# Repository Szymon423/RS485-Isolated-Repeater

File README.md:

# RS485 Isolated Repeater

This project is abotut designing an isolated repeater for RS485 communication. As a person who many times had to deal with RS485 communication, I know how important it is to have a repeater in order to extend the communication distance. However, I also know how important it is to have an isolated repeater in order to avoid ground loops and other issues that can arise from non-isolated repeaters. This project is about designing an isolated repeater that can be used to extend the communication distance of RS485 devices. The repeater is designed to be used with a `12..24V` power supply and can be used to extend the communication distance up to 1000 meters. 

> [!IMPORTANT]
> Chad GPT is amazing and made up this trash talk above.

To be honest this is not about extending range of RS485 loop, even though it can be used for that. It is about isolating the RS485 devices which are shitty and can cause problems. 

> [!NOTE]
> I want to help people who made shitty RS485 bus or RS485 devices.

## Tools stack
- Hardware design: `KiCad`
- PCB manufacturing: `JLCPCB`
- Microcontroller code: `Raspberry Pi Pico Extension for VSCode`
- Knowledge: `IDK`

## Hardware
{:width="200px"}

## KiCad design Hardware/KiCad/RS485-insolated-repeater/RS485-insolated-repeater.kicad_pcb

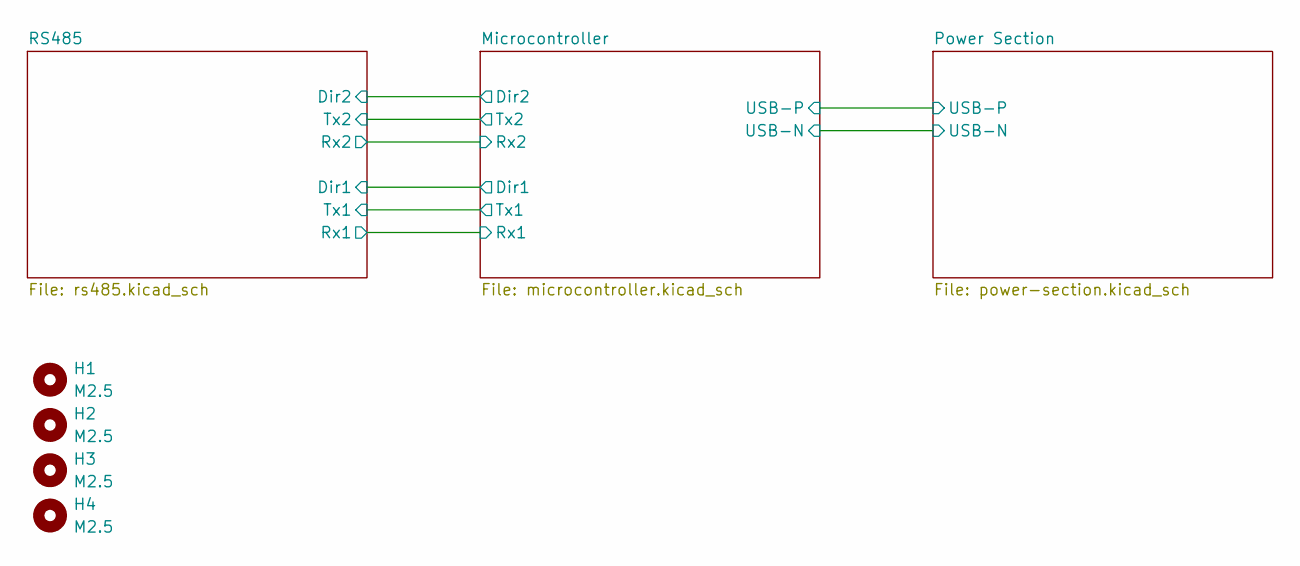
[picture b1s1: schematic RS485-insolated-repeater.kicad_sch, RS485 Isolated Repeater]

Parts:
H1, H2, H3, H4: M2.5; MountingHole_2.7mm_M2.5

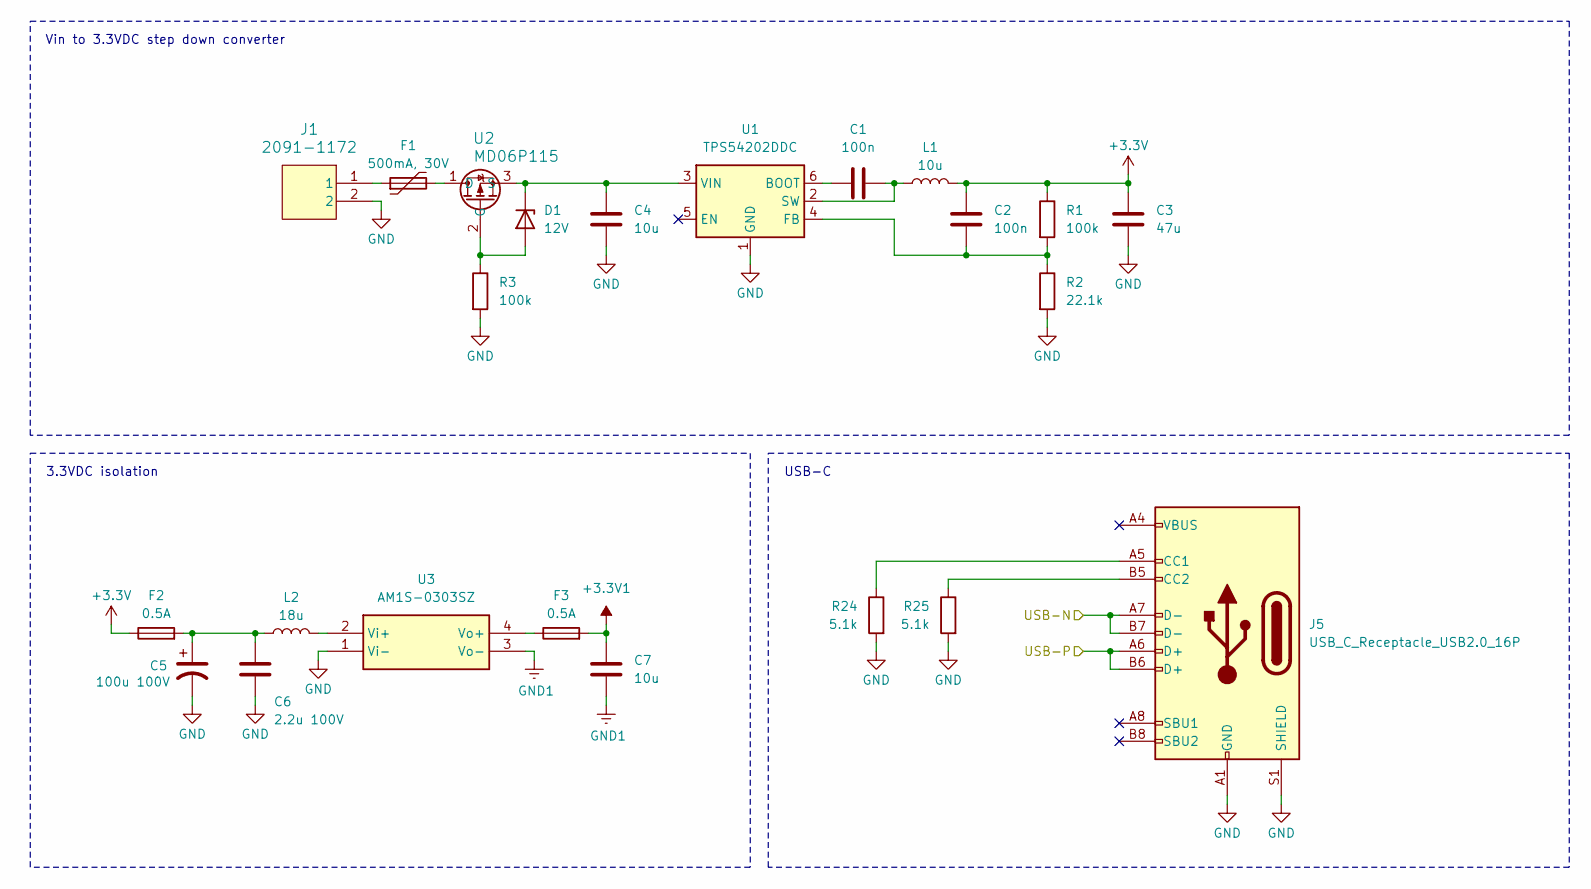
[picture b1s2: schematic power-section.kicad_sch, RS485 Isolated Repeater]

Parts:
C1, C2: 100n; C_0805_2012Metric
C3: 47u; C_1206_3216Metric
C4, C7: 10u; C_1206_3216Metric
C5: 100u 100V; CP_Radial_D10.0mm_P5.00mm
C6: 2.2u 100V; C_1210_3225Metric
D1: 12V; D_SMA
F1: 500mA, 30V; Fuse_1812_4532Metric
F2, F3: 0.5A; Fuse_1206_3216Metric
J1: 2091-1172
J5: USB_C_Receptacle_USB2.0_16P; USB_C_Receptacle_GCT_USB4105-xx-A_16P_TopMnt_Horizontal
L1: 10u; L_12x12mm_H4.5mm
L2: 18u; L_Ferrocore_DLG-0504
R1, R3: 100k; R_0805_2012Metric
R2: 22.1k; R_0805_2012Metric
R24, R25: 5.1k; R_0805_2012Metric
U1: TPS54202DDC; SOT-23-6
U2: MD06P115
U3: AM1S-0303SZ; SON50P300X200X60-9N; Manufacturer_Part_Number W25Q16JVUXIQ TR

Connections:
+3.3V: C2.2, C3.2, F2.1, L1.2, R1.1; also elsewhere on the board
+3.3V1: C7.2, F3.2; also elsewhere on the board
/Microcontroller/USB-N: J5.A7 (D-), J5.B7 (D-); also elsewhere on the board
/Microcontroller/USB-P: J5.A6 (D+), J5.B6 (D+); also elsewhere on the board
GND: C3.1, C4.1, C5.2, C6.2, J1.2, J5.A1 (GND), J5.A12 (GND), J5.B1 (GND), J5.B12 (GND), J5.S1 (SHIELD), R2.2, R3.2, R24.2, R25.2, U1.1 (GND), U3.1 (Vi-); also elsewhere on the board
GND1: C7.1, U3.3 (Vo-); also elsewhere on the board
unnamed: C5.1, C6.1, F2.2, L2.1
unnamed: D1.2 (A), R3.1, U2.2 (G)
unnamed: C4.2, D1.1 (K), U1.3 (VIN), U2.3 (S)
unnamed: F1.1, J1.1
unnamed: J5.A5 (CC1), R24.1
unnamed: J5.B5 (CC2), R25.1
unnamed: C1.1, U1.6 (BOOT)
unnamed: C2.1, R1.2, R2.1, U1.4 (FB)
unnamed: C1.2, L1.1, U1.2 (SW)
unnamed: F1.2, U2.1 (D)
unnamed: L2.2, U3.2 (Vi+)
unnamed: F3.1, U3.4 (Vo+)

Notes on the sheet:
Vin to 3.3VDC step down converter
USB-C
3.3VDC isolation

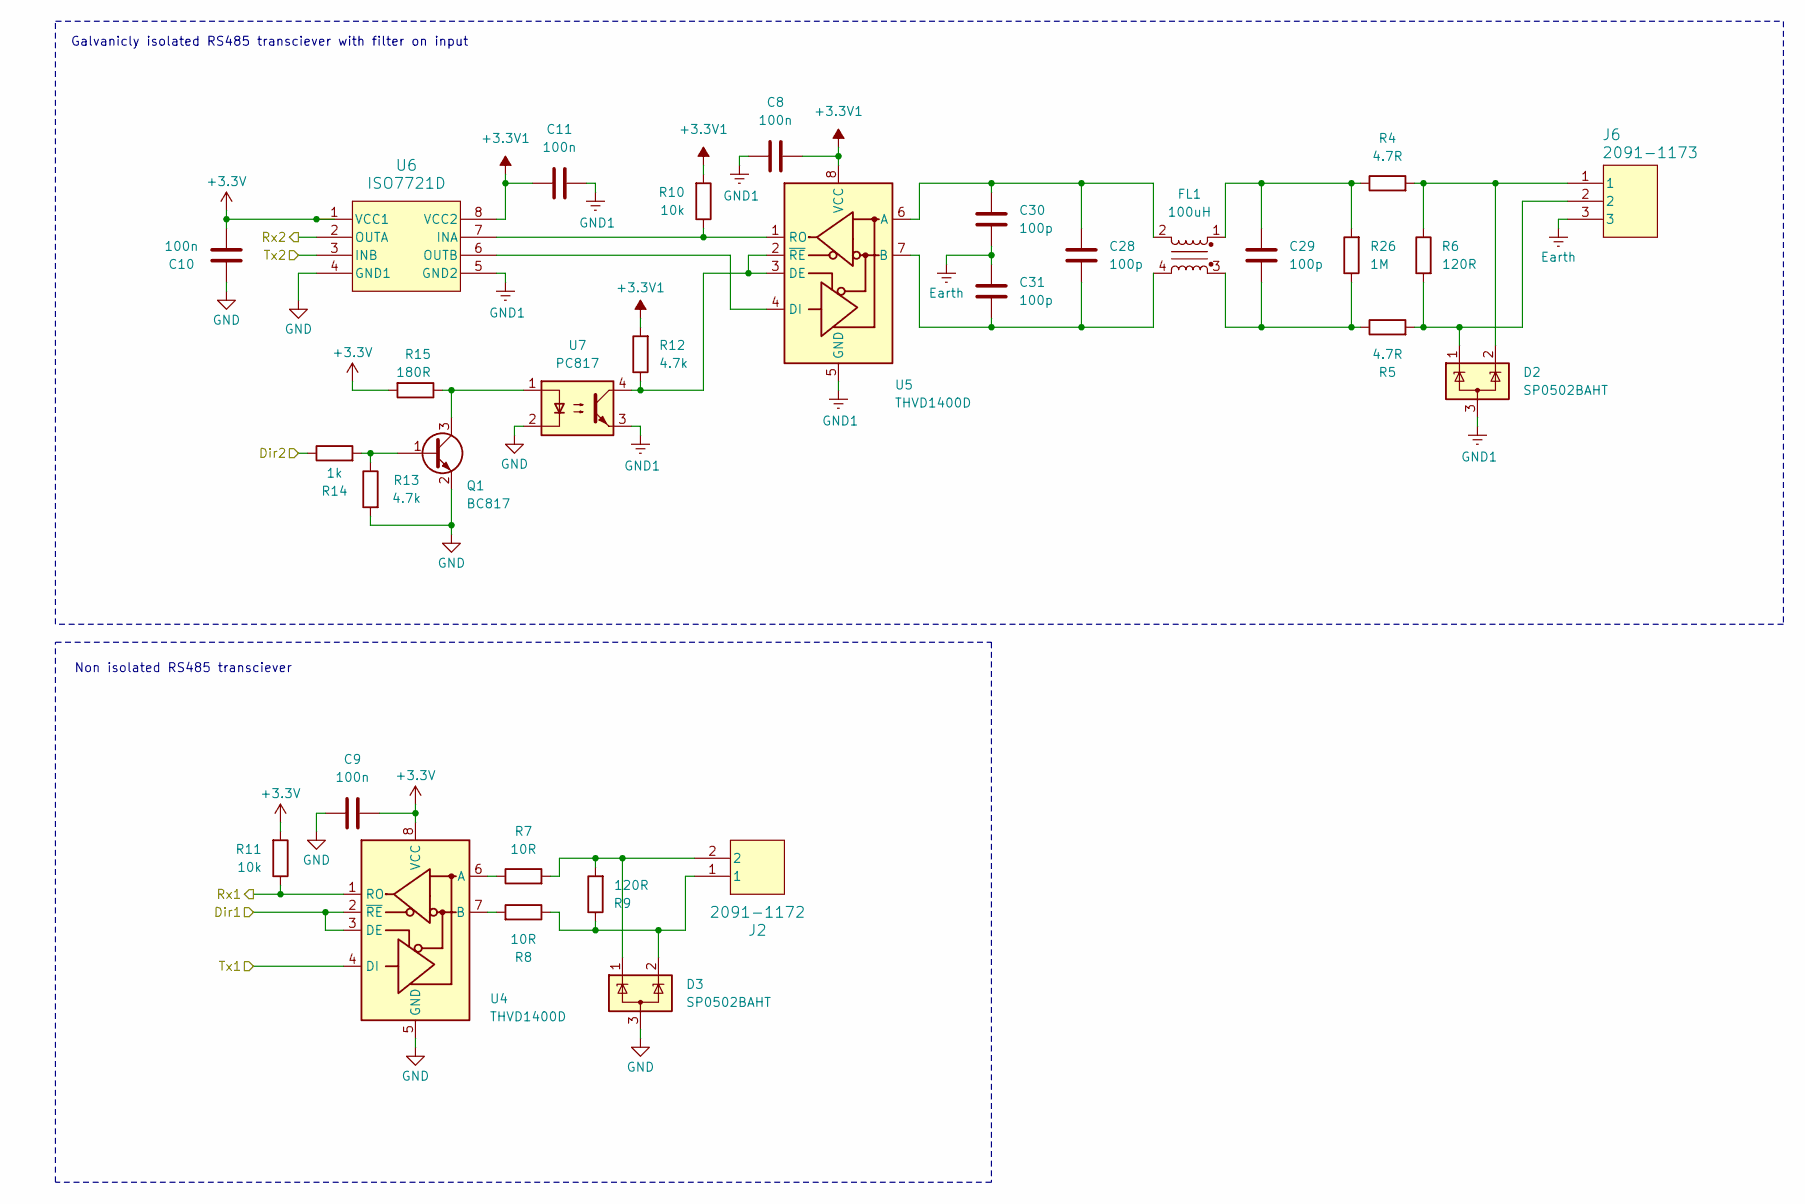
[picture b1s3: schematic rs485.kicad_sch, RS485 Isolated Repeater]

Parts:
C8, C9, C10, C11: 100n; C_0805_2012Metric
C28, C29, C30, C31: 100p; C_0805_2012Metric
D2, D3: SP0502BAHT; SOT-23-3
FL1: 100uH; L_CommonModeChoke_Coilcraft_1812CAN
J2: 2091-1172
J6: 2091-1173
Q1: BC817; SOT-23
R4, R5: 4.7R; R_0805_2012Metric
R6, R9: 120R; R_1206_3216Metric
R7, R8: 10R; R_0805_2012Metric
R10, R11: 10k; R_0805_2012Metric
R12, R13: 4.7k; R_0805_2012Metric
R14: 1k; R_0805_2012Metric
R15: 180R; R_0805_2012Metric
R26: 1M; R_0805_2012Metric
U4, U5: THVD1400D; SOIC-8_3.9x4.9mm_P1.27mm
U6: ISO7721D
U7: PC817; DIP-4_W7.62mm_SMDSocket_SmallPads

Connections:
+3.3V: C9.2, C10.1, R11.2, R15.2, U4.8 (VCC), U6.1 (VCC1); also elsewhere on the board
+3.3V1: C8.2, C11.1, R10.2, R12.2, U5.8 (VCC), U6.8 (VCC2); also elsewhere on the board
/Microcontroller/Dir1: U4.2 (~RE), U4.3 (DE); also elsewhere on the board
/Microcontroller/Dir2: R14.1; also elsewhere on the board
/Microcontroller/Rx1: R11.1, U4.1 (RO); also elsewhere on the board
/Microcontroller/Rx2: U6.2 (OUTA); also elsewhere on the board
/Microcontroller/Tx1: U4.4 (DI); also elsewhere on the board
/Microcontroller/Tx2: U6.3 (INB); also elsewhere on the board
Earth: C30.1, C31.2, J6.3
GND: C9.1, C10.2, D3.3 (A), Q1.2 (E), R13.2, U4.5 (GND), U6.4 (GND1), U7.2; also elsewhere on the board
GND1: C8.1, C11.2, D2.3 (A), U5.5 (GND), U6.5 (GND2), U7.3; also elsewhere on the board
unnamed: C29.1, FL1.3, R5.1, R26.1
unnamed: C29.2, FL1.1, R4.1, R26.2
unnamed: D2.1 (K), J6.2, R5.2, R6.2
unnamed: D2.2 (K), J6.1, R4.2, R6.1
unnamed: D3.1 (K), J2.2, R7.2, R9.2
unnamed: D3.2 (K), J2.1, R8.1, R9.1
unnamed: Q1.1 (B), R13.1, R14.2
unnamed: Q1.3 (C), R15.1, U7.1
unnamed: R7.1, U4.6 (A)
unnamed: R8.2, U4.7 (B)
unnamed: C28.2, C30.2, FL1.2, U5.6 (A)
unnamed: C28.1, C31.1, FL1.4, U5.7 (B)
unnamed: R12.1, U5.2 (~RE), U5.3 (DE), U7.4
unnamed: U5.4 (DI), U6.6 (OUTB)
unnamed: R10.1, U5.1 (RO), U6.7 (INA)

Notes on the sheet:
Non isolated RS485 transciever
Galvanicly isolated RS485 transciever with filter on input

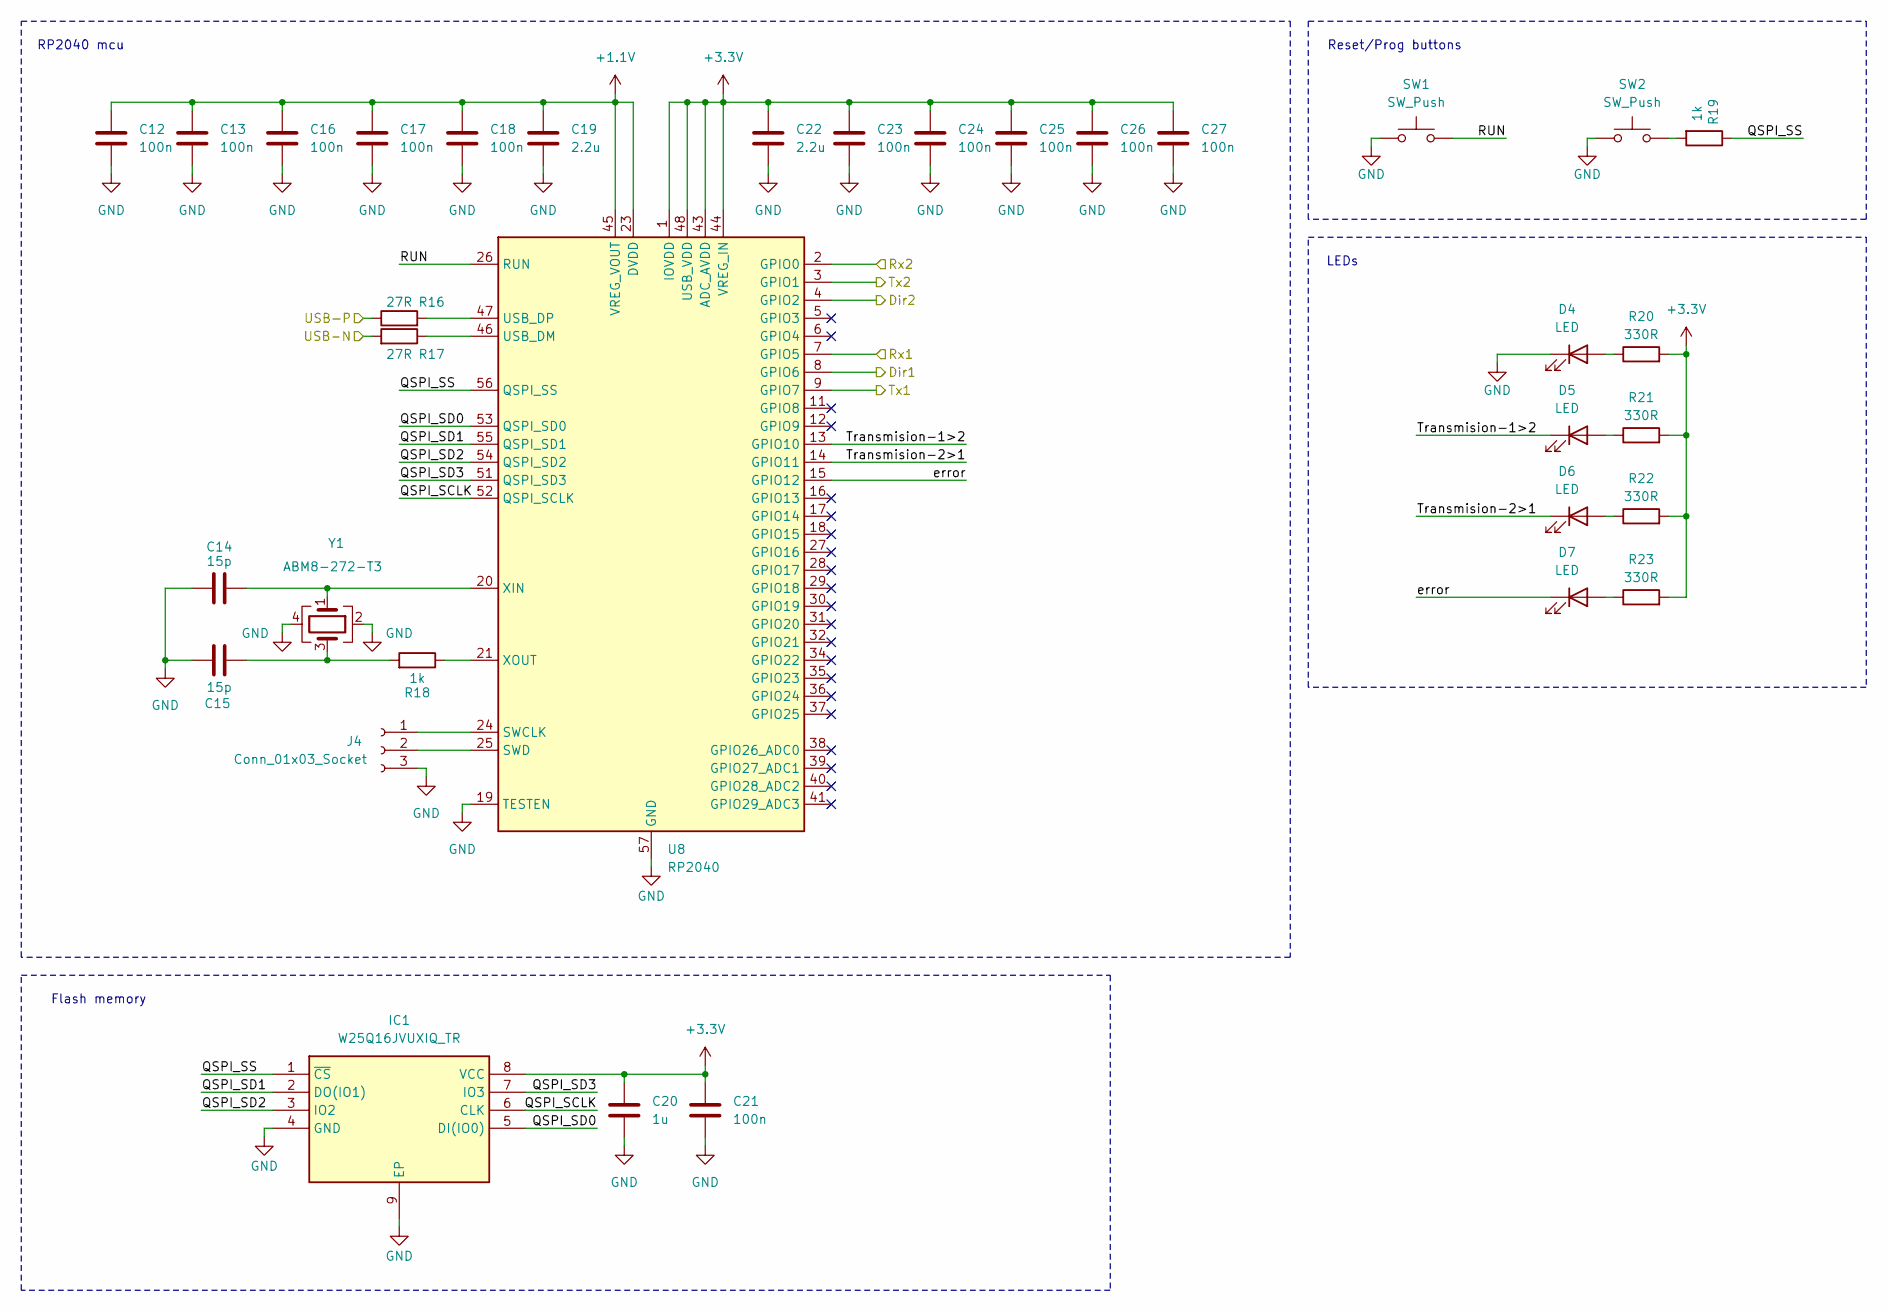
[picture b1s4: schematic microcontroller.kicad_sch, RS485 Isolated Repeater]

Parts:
C12, C13, C16, C17, C18, C21, C23, C24, C25, C26, C27: 100n; C_0402_1005Metric
C14, C15: 15p; C_0402_1005Metric
C19, C22: 2.2u; C_0805_2012Metric
C20: 1u; C_0805_2012Metric
D4, D5, D6, D7: LED; LED_0805_2012Metric
IC1: W25Q16JVUXIQ_TR; SON50P300X200X60-9N; Manufacturer_Part_Number W25Q16JVUXIQ TR
J4: Conn_01x03_Socket; JST_PH_S3B-PH-K_1x03_P2.00mm_Horizontal
R16, R17: 27R; R_0402_1005Metric
R18, R19: 1k; R_0402_1005Metric
R20, R21, R22, R23: 330R; R_0805_2012Metric
SW1, SW2: SW_Push; SW_Tactile_SPST_NO_Straight_CK_PTS636Sx25SMTRLFS
U8: RP2040; QFN-56-1EP_7x7mm_P0.4mm_EP3.2x3.2mm_ThermalVias
Y1: ABM8-272-T3; Crystal_SMD_Abracon_ABM3B-4Pin_5.0x3.2mm

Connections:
+1.1V: C12.1, C13.1, C16.1, C17.1, C18.1, C19.1, U8.23 (DVDD), U8.45 (VREG_VOUT), U8.50 (DVDD)
+3.3V: C20.1, C21.1, C22.1, C23.1, C24.1, C25.1, C26.1, C27.1, IC1.8 (VCC), R20.2, R21.2, R22.2, R23.2, U8.1 (IOVDD), U8.10 (IOVDD), U8.22 (IOVDD), U8.33 (IOVDD), U8.42 (IOVDD), U8.43 (ADC_AVDD), U8.44 (VREG_IN), U8.48 (USB_VDD), U8.49 (IOVDD); also elsewhere on the board
/Microcontroller/Dir1: U8.8 (GPIO6); also elsewhere on the board
/Microcontroller/Dir2: U8.4 (GPIO2); also elsewhere on the board
/Microcontroller/QSPI_SCLK: IC1.6 (CLK), U8.52 (QSPI_SCLK)
/Microcontroller/QSPI_SD0: IC1.5 (DI(IO0)), U8.53 (QSPI_SD0)
/Microcontroller/QSPI_SD1: IC1.2 (DO(IO1)), U8.55 (QSPI_SD1)
/Microcontroller/QSPI_SD2: IC1.3 (IO2), U8.54 (QSPI_SD2)
/Microcontroller/QSPI_SD3: IC1.7 (IO3), U8.51 (QSPI_SD3)
/Microcontroller/QSPI_SS: IC1.1 (~CS), R19.1, U8.56 (QSPI_SS)
/Microcontroller/RUN: SW1.2, U8.26 (RUN)
/Microcontroller/Rx1: U8.7 (GPIO5); also elsewhere on the board
/Microcontroller/Rx2: U8.2 (GPIO0); also elsewhere on the board
/Microcontroller/Transmision-1>2: D5.1 (K), U8.13 (GPIO10)
/Microcontroller/Transmision-2>1: D6.1 (K), U8.14 (GPIO11)
/Microcontroller/Tx1: U8.9 (GPIO7); also elsewhere on the board
/Microcontroller/Tx2: U8.3 (GPIO1); also elsewhere on the board
/Microcontroller/USB-N: R17.2; also elsewhere on the board
/Microcontroller/USB-P: R16.1; also elsewhere on the board
/Microcontroller/error: D7.1 (K), U8.15 (GPIO12)
GND: C12.2, C13.2, C14.1, C15.1, C16.2, C17.2, C18.2, C19.2, C20.2, C21.2, C22.2, C23.2, C24.2, C25.2, C26.2, C27.2, D4.1 (K), IC1.4 (GND), IC1.9 (EP), J4.3, SW1.1, SW2.1, U8.19 (TESTEN), U8.57 (GND), Y1.2, Y1.4; also elsewhere on the board
unnamed: C15.2, R18.2, Y1.3
unnamed: D4.2 (A), R20.1
unnamed: D5.2 (A), R21.1
unnamed: D6.2 (A), R22.1
unnamed: D7.2 (A), R23.1
unnamed: J4.1, U8.24 (SWCLK)
unnamed: J4.2, U8.25 (SWD)
unnamed: R19.2, SW2.2
unnamed: R17.1, U8.46 (USB_DM)
unnamed: R16.2, U8.47 (USB_DP)
unnamed: C14.2, U8.20 (XIN), Y1.1
unnamed: R18.1, U8.21 (XOUT)

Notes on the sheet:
LEDs
Reset/Prog buttons
RP2040 mcu
Flash memory

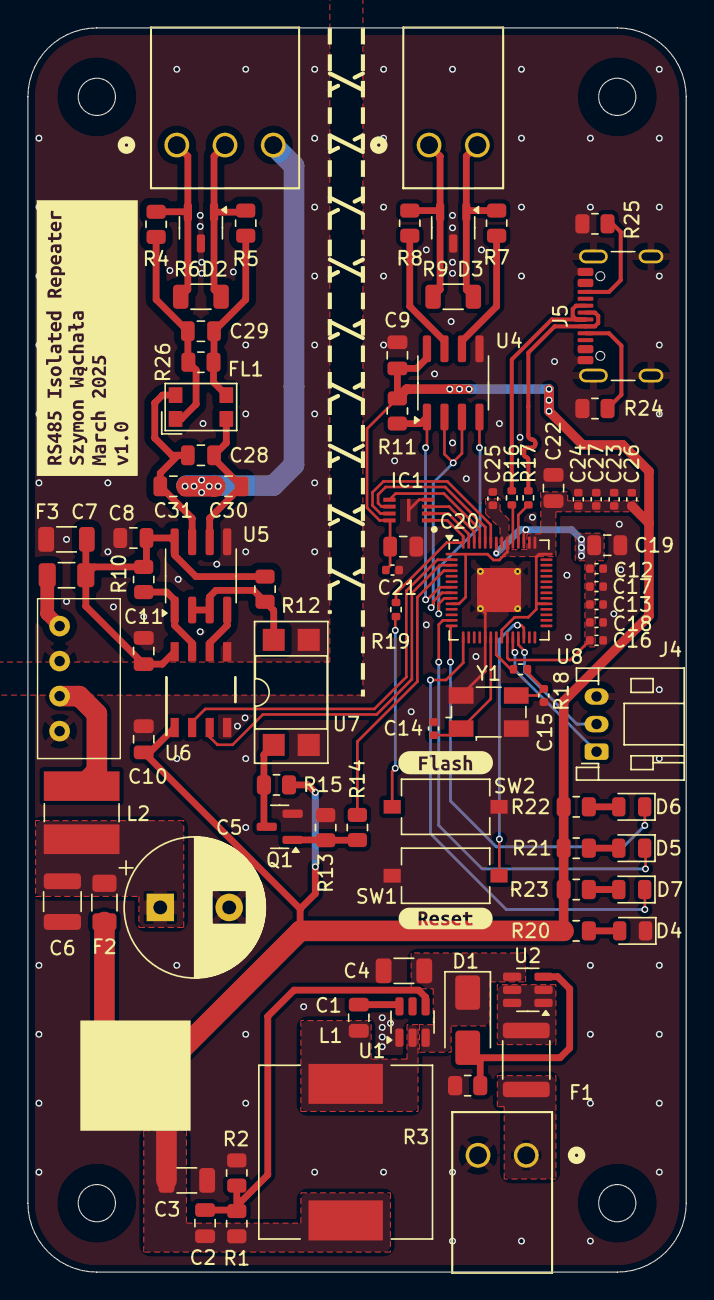
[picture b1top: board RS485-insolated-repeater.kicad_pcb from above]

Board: 2 copper layers, 47.7 x 90.2 mm, 95 parts (0 on the bottom side), 63 nets.

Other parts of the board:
kibuzzard-67E01B78: G***; kibuzzard-67E01B78
kibuzzard-67E01C2F: G***; kibuzzard-67E01C2F
kibuzzard-67E01C3D: G***; kibuzzard-67E01C3D

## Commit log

2025-03-23 added cool readme and empty gitignore
2025-03-23 Added 3D model
2025-03-23 Added renders
2025-03-23 Started writing code - gpio, interrupts
